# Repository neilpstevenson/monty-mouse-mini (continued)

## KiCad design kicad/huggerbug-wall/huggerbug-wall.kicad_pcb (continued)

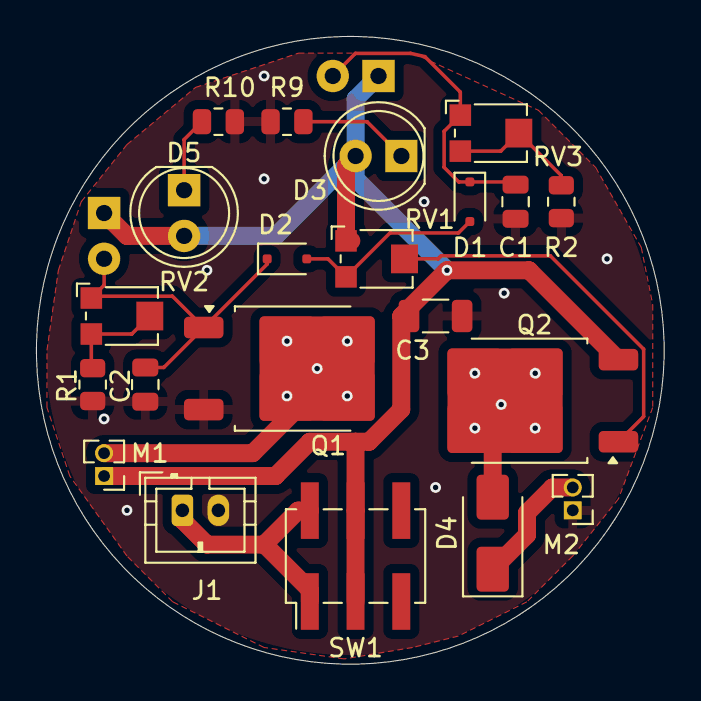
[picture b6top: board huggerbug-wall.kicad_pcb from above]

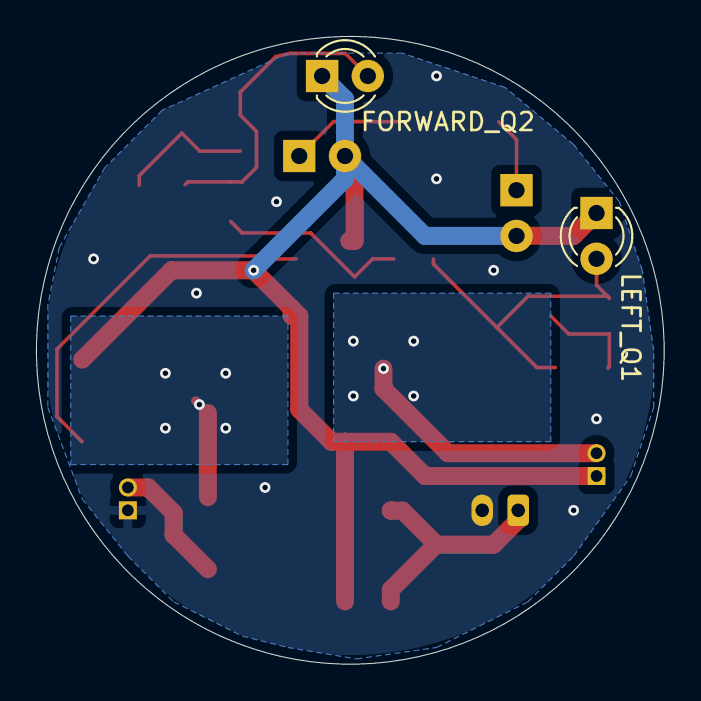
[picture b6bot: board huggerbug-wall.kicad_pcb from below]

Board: 2 copper layers, 34.9 x 34.9 mm, 23 parts (2 on the bottom side), 14 nets.

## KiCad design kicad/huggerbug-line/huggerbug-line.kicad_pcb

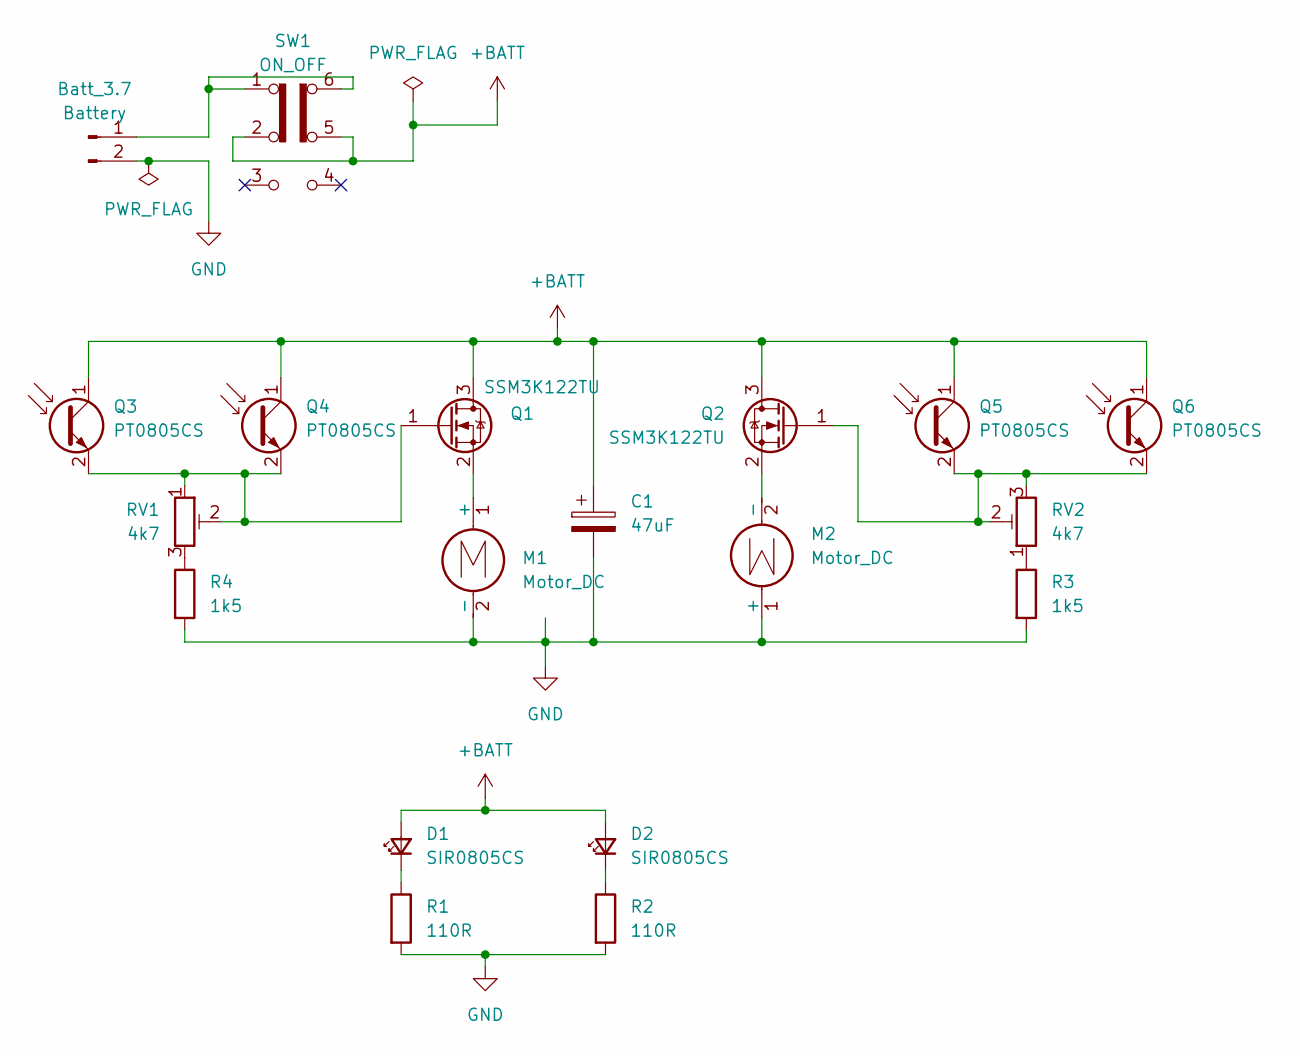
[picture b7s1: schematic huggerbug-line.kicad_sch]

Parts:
Batt_3.7: Battery; JST_PH_B2B-PH-K_1x02_P2.00mm_Vertical
C1: 47uF; CP_Elec_5x5.4
D1, D2: SIR0805CS; LED_0805_2012Metric_Pad1.15x1.40mm_HandSolder
M1, M2: Motor_DC; PinHeader_1x02_P1.27mm_Vertical
Q1, Q2: SSM3K122TU; SOT-323_SC-70
Q3, Q4, Q5, Q6: PT0805CS; LED_0805_2012Metric_Pad1.15x1.40mm_HandSolder
R1, R2: 110R; R_0805_2012Metric
R3, R4: 1k5; R_0805_2012Metric
RV1, RV2: 4k7; Potentiometer_Bourns_TC33X_Vertical
SW1: ON_OFF; PinSocket_2x03_P2.54mm_Vertical_SMD

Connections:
+BATT: C1.1, D1.2 (A), D2.2 (A), Q1.3 (D), Q2.3 (D), Q3.1 (C), Q4.1 (C), Q5.1 (C), Q6.1 (C), SW1.2 (B), SW1.5 (B)
GND: Batt_3.7.2, C1.2, M1.2 (-), M2.1 (+), R1.2, R2.2, R3.2, R4.2
unnamed: Batt_3.7.1, SW1.1 (A), SW1.6 (C)
unnamed: D1.1 (K), R1.1
unnamed: D2.1 (K), R2.1
unnamed: M1.1 (+), Q1.2 (S)
unnamed: M2.2 (-), Q2.2 (S)
unnamed: Q1.1 (G), Q3.2 (E), Q4.2 (E), RV1.1, RV1.2
unnamed: Q2.1 (G), Q5.2 (E), Q6.2 (E), RV2.2, RV2.3
unnamed: R3.1, RV2.1
unnamed: R4.1, RV1.3

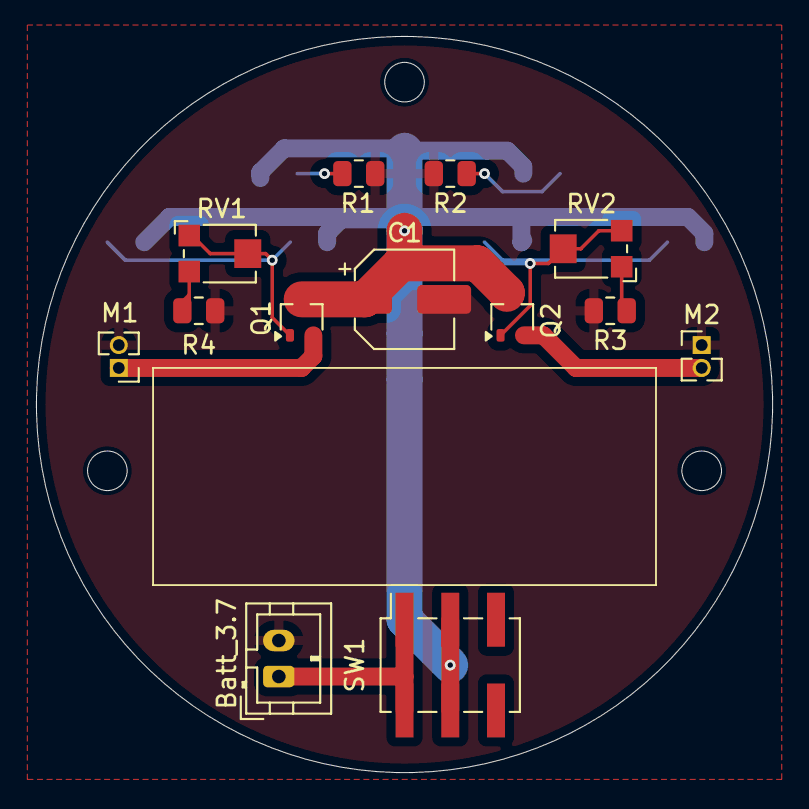
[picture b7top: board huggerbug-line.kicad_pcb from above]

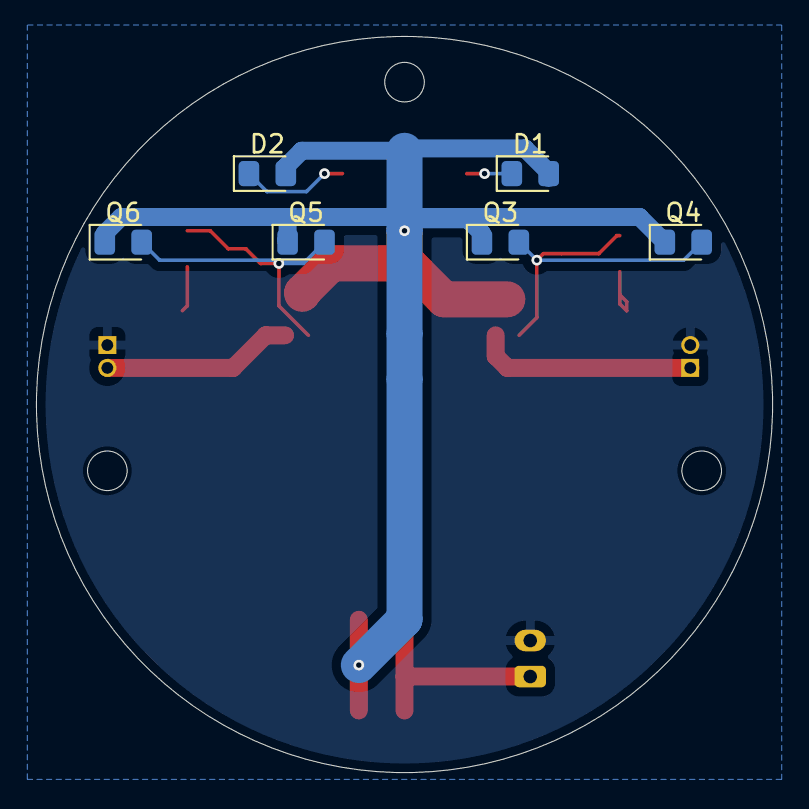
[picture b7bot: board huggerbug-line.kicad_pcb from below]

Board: 2 copper layers, 40.9 x 40.9 mm, 22 parts (6 on the bottom side), 11 nets.

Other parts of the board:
Hole: MountingHole_2.2mm_M2
Hole#2, Hole#3: MountingHole_2.2mm_M2

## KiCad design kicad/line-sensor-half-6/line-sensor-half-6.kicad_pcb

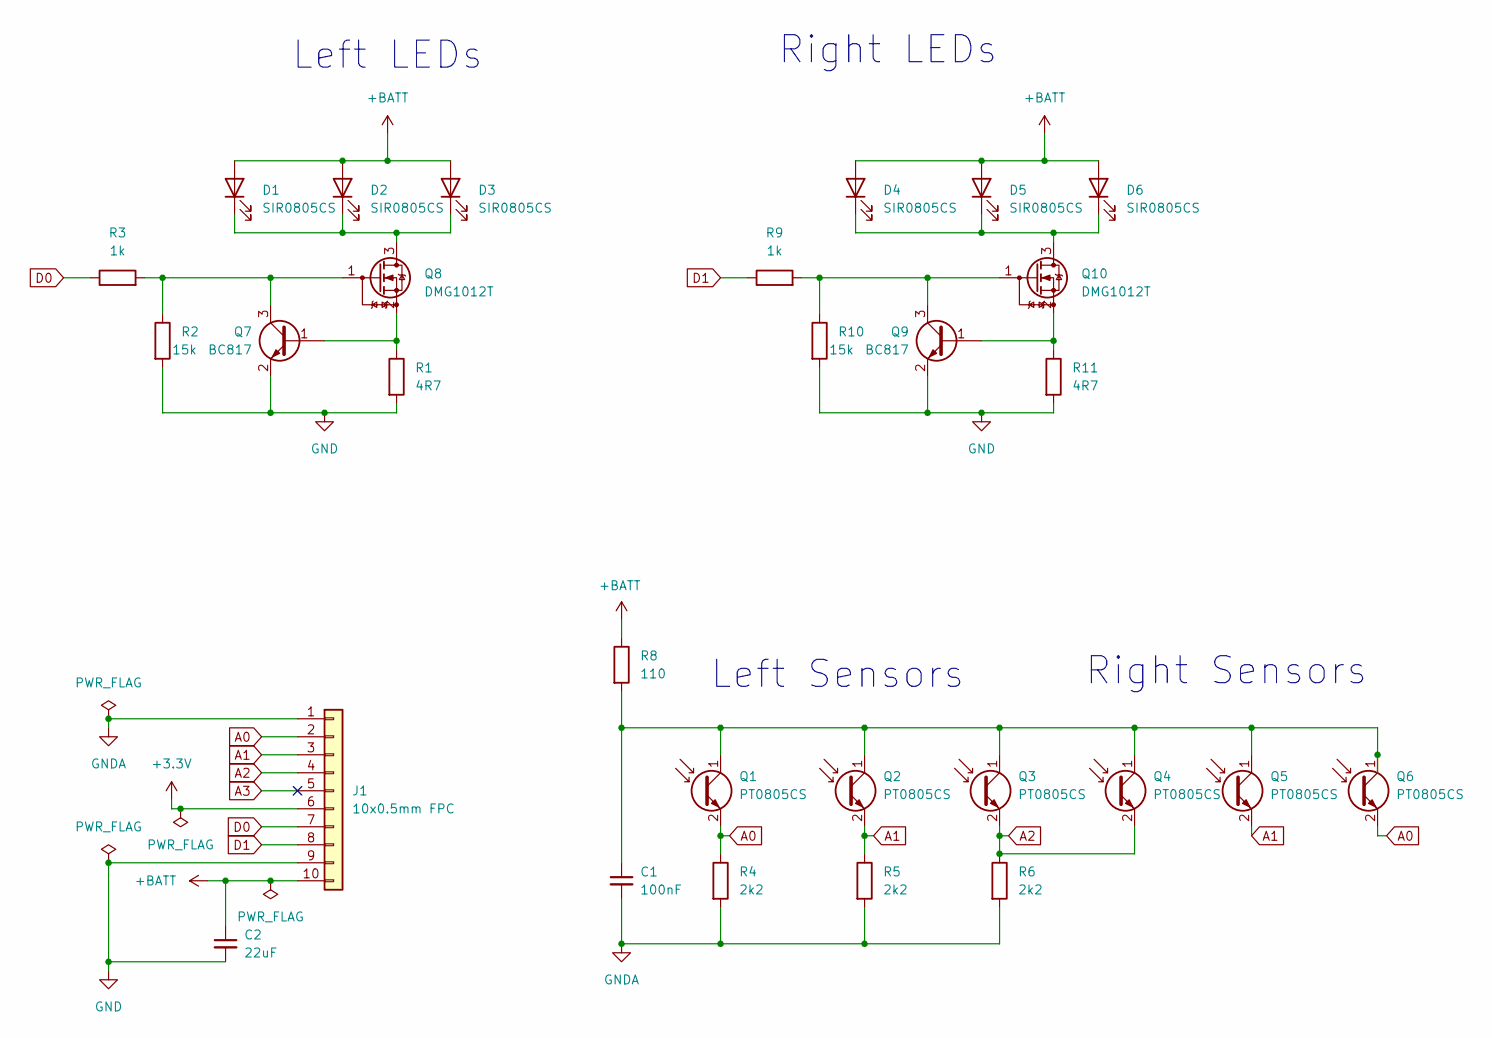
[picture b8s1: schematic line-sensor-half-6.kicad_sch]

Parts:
C1: 100nF; C_0805_2012Metric
C2: 22uF; C_0805_2012Metric
D1, D2, D3, D4, D5, D6: SIR0805CS; LED_0805_2012Metric_Pad1.15x1.40mm_HandSolder
J1: 10x0.5mm FPC; SlimFPC_1x10-1MP_P0.5mm_Horizontal
Q1, Q2, Q3, Q4, Q5, Q6: PT0805CS; LED_0805_2012Metric_Pad1.15x1.40mm_HandSolder
Q7, Q9: BC817; SOT-23
Q8, Q10: DMG1012T; SOT-523
R1, R11: 4R7; R_0805_2012Metric
R2, R10: 15k; R_0805_2012Metric
R3, R9: 1k; R_0805_2012Metric
R4, R5, R6: 2k2; R_0805_2012Metric
R8: 110; R_0805_2012Metric

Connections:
+3.3V: J1.6
+BATT: C2.1, D1.2 (A), D2.2 (A), D3.2 (A), D4.2 (A), D5.2 (A), D6.2 (A), J1.10, R8.1
A0: J1.2, Q1.2 (E), Q6.2 (E), R4.1
A1: J1.3, Q2.2 (E), Q5.2 (E), R5.1
A2: J1.4, Q3.2 (E), Q4.2 (E), R6.1
A3: J1.5
D0: J1.7, R3.1
D1: J1.8, R9.1
GND: C2.2, J1.9, Q7.2 (E), Q9.2 (E), R1.2, R2.2, R10.2, R11.2
GNDA: C1.2, J1.1, R4.2, R5.2, R6.2
unnamed: D1.1 (K), D2.1 (K), D3.1 (K), Q8.3 (D)
unnamed: D4.1 (K), D5.1 (K), D6.1 (K), Q10.3 (D)
unnamed: C1.1, Q1.1 (C), Q2.1 (C), Q3.1 (C), Q4.1 (C), Q5.1 (C), Q6.1 (C), R8.2
unnamed: Q7.1 (B), Q8.2 (S), R1.1
unnamed: Q7.3 (C), Q8.1 (G), R2.1, R3.2
unnamed: Q9.3 (C), Q10.1 (G), R9.2, R10.1
unnamed: Q9.1 (B), Q10.2 (S), R11.1

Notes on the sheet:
Right LEDs
Left Sensors
Right Sensors
Left LEDs

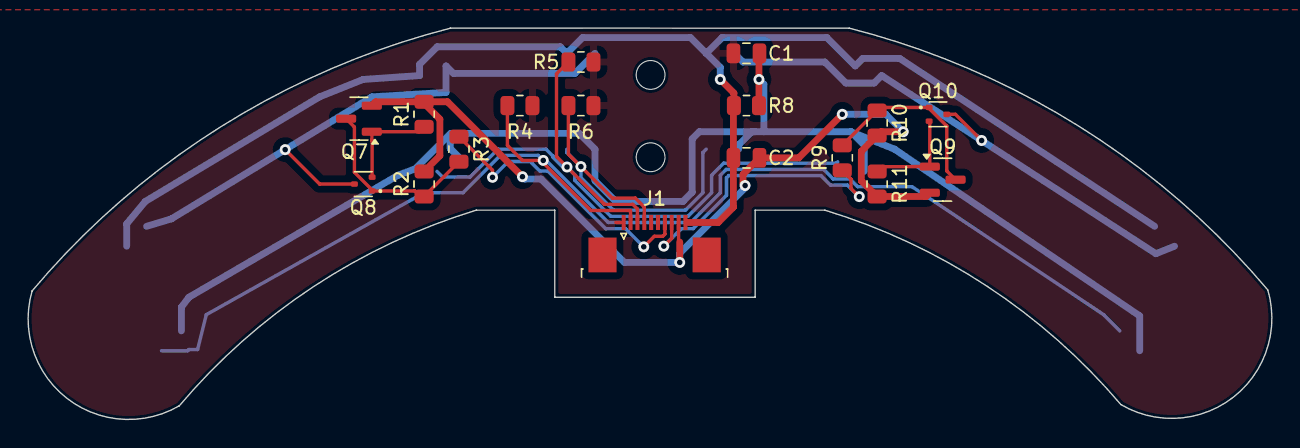
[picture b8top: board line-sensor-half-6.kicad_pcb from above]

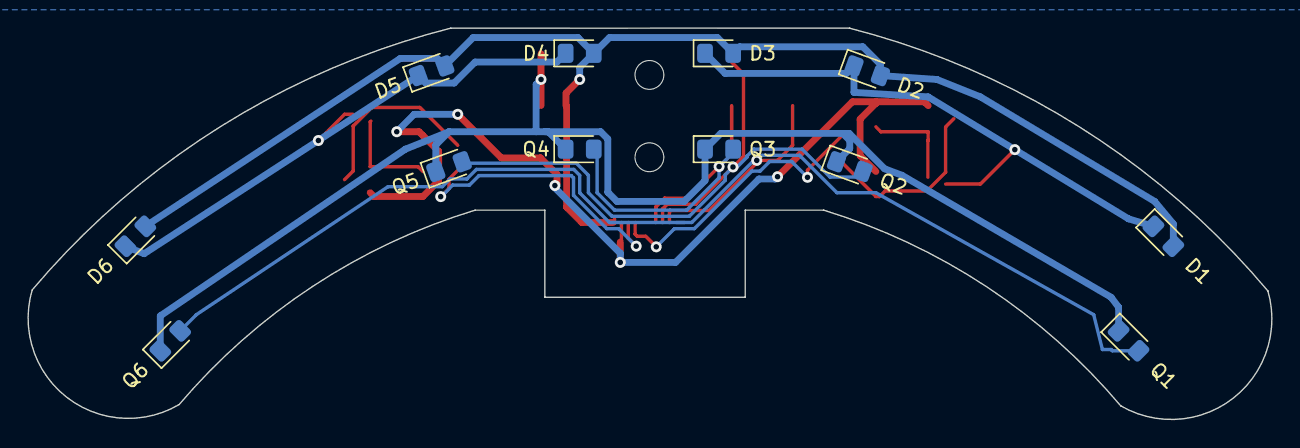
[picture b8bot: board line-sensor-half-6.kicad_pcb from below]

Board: 2 copper layers, 90.7 x 28.5 mm, 31 parts (12 on the bottom side), 15 nets.

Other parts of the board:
REF-mh: MountingHole_2.1mm
REF-mh#2: MountingHole_2.1mm

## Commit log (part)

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2022-03-30 Initial version of dragster test code
2022-03-30 tuning
2022-04-01 Dragster tuning
2022-04-04 Changes in preparation for Minos2022
2022-06-05 Add line follower KiCad board
2022-06-08 Add steering calibration. Add test code for acceleration profile runs.
2022-06-09 Add profiled runs for faster speeds
2022-06-12 Move over to new profiled runner. Start to refactor h/w code
2022-06-20 Snapshot & new hardware defaults with nv-ram PID config
2022-06-20 More tidy up ready for 2022 tech fest comp
2022-07-05 Add new dragster main board pcb
2022-07-17 Techfest 2022 final version run
2022-08-06 Add new motor controller option. Initial bluetooth pair option (doesn't work!)
2022-08-06 Add bluetooth config
2022-08-06 Initial refactor to Motors class
2022-08-07 Add pwm with break option
2022-08-10 Add bluetooth pairing test code
2022-08-11 Remove redundant pairing/hid code. Add display of pairing info
2022-08-14 Add motor encoders support - calibration only currently
2022-08-21 Add encoder display
2022-08-29 Add more distance & speed-base profile capabilities. Small track testing and tuning.
2022-08-29 Tweak crazy profile
2022-08-29 Minor teaks to fix hole sizes and some positions
2022-09-01 Tune runs - all OK for old 11:54 gear ratio drive. Add stats gathering & display
2022-09-02 Improve speed assessment Tuning for new gearing/motors
2022-09-02 Revert main to old prototype version
2022-09-22 Add new line sensor PCB
2022-09-22 Add new XIAO-based main pcb
2022-09-22 Tune for full course runs
2022-09-26 Changes to permit start via Radius sensor without PS4 controller
2022-09-26 Revert previous merge
2022-09-26 Some refactoring
2022-09-26 Further refactoring
2022-10-28 Add new monti 1/2 size pcb main board
2022-10-31 Sensor board first draft
2022-10-31 Snapshot 2
2022-10-31 Final tweaks
2022-10-31 V1.0 for production
2023-01-28 Add test wall follower code
2023-02-26 Add distance encoder moves
2023-03-08 Development
2023-03-08 Initial fixes
2023-03-12 Config tweaks
2023-03-12 Improve 180 degree and u-turns
2023-03-17 Increase stopping distance by 0.1secs
2023-03-20 Tweak for Spring 2023 competition
2023-04-11 Updates for v2.0 of HalfMonty PCBs
2023-04-11 Final updates for v2.0 of boards & export
2023-05-08 Update component values on PCBs. Fix PCB labelling R2/R5 issue.
2023-05-08 Add test project
2023-06-28 Updates for new hardware revision and software improvements
2023-06-30 Tweaks for summer 2023
2023-06-30 Rework to follow right & left walls, and also attempt to follow before and after turns. Ready for summer 2023 competition!
2023-09-02 Add v2 board designs for dragster
2023-09-02 Final tweaks before v2 to JLCPCB manufacture
2023-09-08 Add MX1508Adapter KiCad
2023-09-25 Changes for new Hammer Mouse III PCBs with SMT sensors. Centralise sensor reading to single function and add ambient light compensation. Add buttons to abort run. Move gauge displays to single functi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
2023-09-29 More changes for Hammer Mouse III. Improve sensor/PID loop times. Fix sensor/PID steering orientation. Add Up support to menu navigation
2023-09-29 Fix off-track detection. Change loop frequency to 200Hz, which should give better PID results
2023-10-01 Try to improve stability of readings by doing 4-way averaging. Put loop speed to 4mS.
2023-10-16 Add logging to serial port. Misc UI improvements and full maze parameters.
2024-03-12 Add simple wall follower code for UKMARS Summer 2024
2024-03-25 Add new sensor boards and adapters designs
2024-03-25 Updates to older pcbs
2024-03-25 Final tweaks for MINOS spring 2024 competition
2024-09-27 Initial port of mazerunner core
2024-09-27 Update to motor control for latest ESP32 code base
2024-09-30 Snapshot
2024-09-30 Base configuration & tuning
2024-10-01 Snapshot - seems to be ok for now!
2024-10-02 Add function select via the button and neopixel indicator
2024-10-02 Add left/right turn LEDs
2024-10-03 Fix reset_count()
2024-10-03 Comments
2024-10-03 Motor lab for HalfMonty
2024-10-04 Enhance encoder use to have finer resolution. Add ACCFF config command. Also rotate right motor, so can test on the ground
2024-10-04 Enhance encoders to use speed derived from timed encoder transitions, due to low resolution otherwise. Adjust robot configuration accordingly, which now behaves differently.
2024-10-06 Tweaks following run at Hazlemere 2024 - fix PID error constraint and slower turning
2024-10-06 Calibration of real maze walls at Hazelmere 2024 competition (Bernard's).
2024-11-25 Add new kicad files for line follower and simple wall & line followers
2025-03-23 Add test code for new 1/2 size line-follower mouse
2025-03-25 Implement ATOMIC critical sections. Implement non-ISR-based SysTick thread, so doesn't interferer with encoder interrupts Move USE_USB_SERIAL_PORT macro so works! Change encoder distance back to orig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
2025-03-27 Update ticker thread priority to REAL_TIME to get less jitter in sensor code. Improve switch display to all > 7 switch codes to be selected and shown. Add flash at start to show the mouse is alive. U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
2025-03-28 Improve initial indicator flash
2025-04-01 Add Monty Pi version of Mazerunner-Core
2025-04-02 Configure for April 2025 event.
2025-04-06 Config tweaks during Spring 2025 Stratford-upon-Avon contest.
2025-06-23 Updates for Ipswich 2025 summer competition
2025-07-24 Add new v2 of the half-size RP2040-Zero mini board
2025-07-24 Add new mini wall sensor board using the standard FPC connection and 4 SMT LEDs/Phototransitors
2025-07-24 Add test code for half-size board
2025-08-27 V1 half-line/wall sensor boards
2025-10-02 Tune simple line follower to go much faster - setting 10 pretty good!
2025-10-03 Bit more tuning - still wobbly!
2025-10-12 New version of wall-follower for full size. Add new design Half-Monty-2
2025-10-21 Add missing sensor schematic (untitled?)
2025-10-21 Rename sensors schematic file
2025-11-04 Update component values after prototype assembly
2025-11-04 Add encoder PCB
2025-11-04 Move test sketch
2025-11-04 Improve test code - PWM freq and type of sensor board
